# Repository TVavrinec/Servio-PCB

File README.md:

# Servio PCB

| pin | function | description |
| --- | -------- | ---- |
| C1  | GND | ground for main connector |
| C2  | VCC | input power for main connector |
| C3  | TX | UART communication TX pin |
| C4  | RX | UART communication RX pin |
| S1  | ENC.CLK,POT.OUT | CLK for SPI encoder, input pin for potentiometer |
| S2  | ENC.MISO,QE.CHB | MISO for SPI encoder, B channel for quadrature encoder |
| S3  | ENC.MOSI,QE.CHA | MOSI for SPI encoder, A channel for quadrature encoder |
| S4  | GND | GND for side connector |
| S5  | VDD 3V3 | MCU voltage for side connector |
| M1  | M1 | motor pin 1 |
| M2  | M2 | motor pin 2 |
| B1  | VDD 3V3 | voltage for boot mode |
| B2  | BOOT0 | pin triggering boot mode |

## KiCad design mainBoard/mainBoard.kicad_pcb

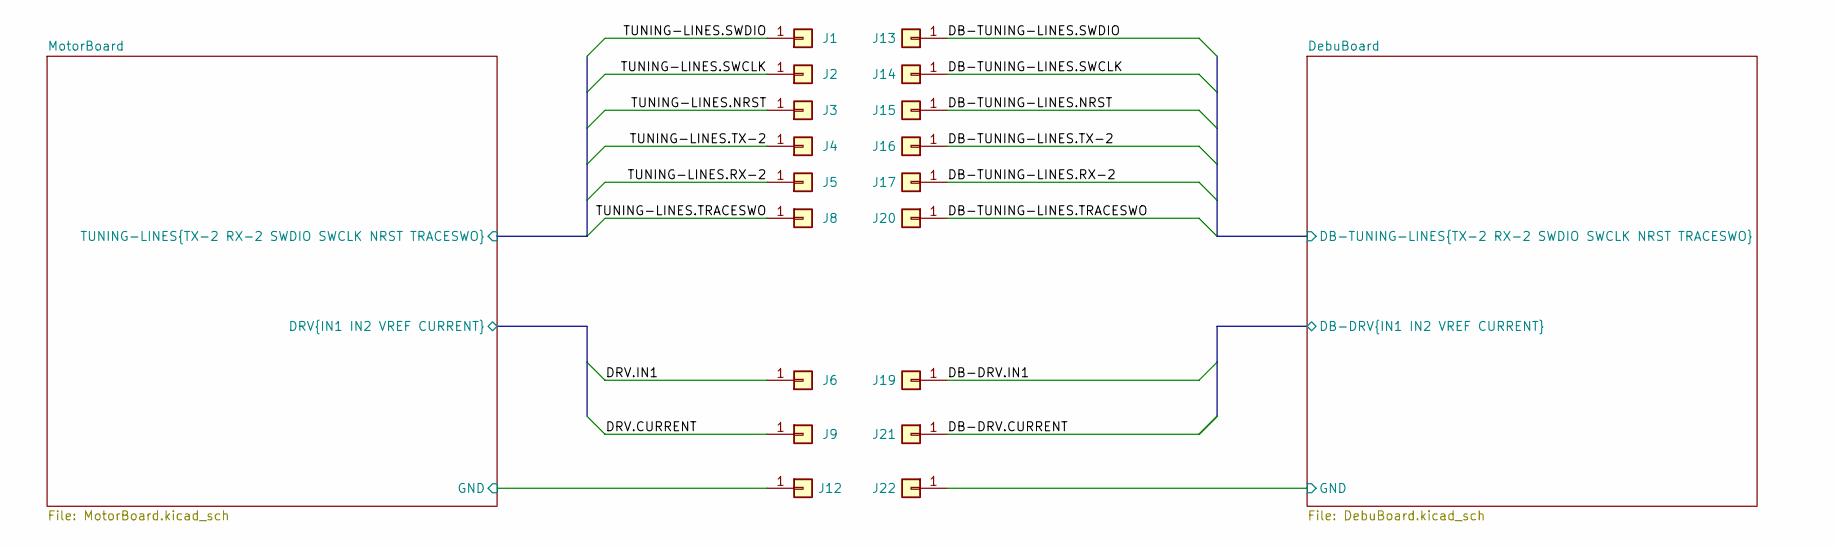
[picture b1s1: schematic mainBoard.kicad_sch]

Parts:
J1, J2, J3, J4, J5, J6, J8, J9, J12: Conn_01x01; YZ157015035P-01-contact_pad; JLCPCB_IGNORE 1
J13, J14, J15, J16, J17, J19, J20, J21, J22: Conn_01x01; YZ157015035P-01; LCSC C5157325

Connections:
/DebuBoard/DB-DRV.CURRENT: J21.1; also elsewhere on the board
/DebuBoard/DB-DRV.IN1: J19.1; also elsewhere on the board
/DebuBoard/DB-TUNING-LINES.NRST: J15.1; also elsewhere on the board
/DebuBoard/DB-TUNING-LINES.RX-2: J17.1; also elsewhere on the board
/DebuBoard/DB-TUNING-LINES.SWCLK: J14.1; also elsewhere on the board
/DebuBoard/DB-TUNING-LINES.SWDIO: J13.1; also elsewhere on the board
/DebuBoard/DB-TUNING-LINES.TRACESWO: J20.1; also elsewhere on the board
/DebuBoard/DB-TUNING-LINES.TX-2: J16.1; also elsewhere on the board
/DebuBoard/GND: J22.1; also elsewhere on the board
/MotorBoard/DRV.CURRENT: J9.1; also elsewhere on the board
/MotorBoard/DRV.IN1: J6.1; also elsewhere on the board
/MotorBoard/TUNING-LINES.NRST: J3.1; also elsewhere on the board
/MotorBoard/TUNING-LINES.RX-2: J5.1; also elsewhere on the board
/MotorBoard/TUNING-LINES.SWCLK: J2.1; also elsewhere on the board
/MotorBoard/TUNING-LINES.SWDIO: J1.1; also elsewhere on the board
/MotorBoard/TUNING-LINES.TRACESWO: J8.1; also elsewhere on the board
/MotorBoard/TUNING-LINES.TX-2: J4.1; also elsewhere on the board
GND: J12.1; also elsewhere on the board

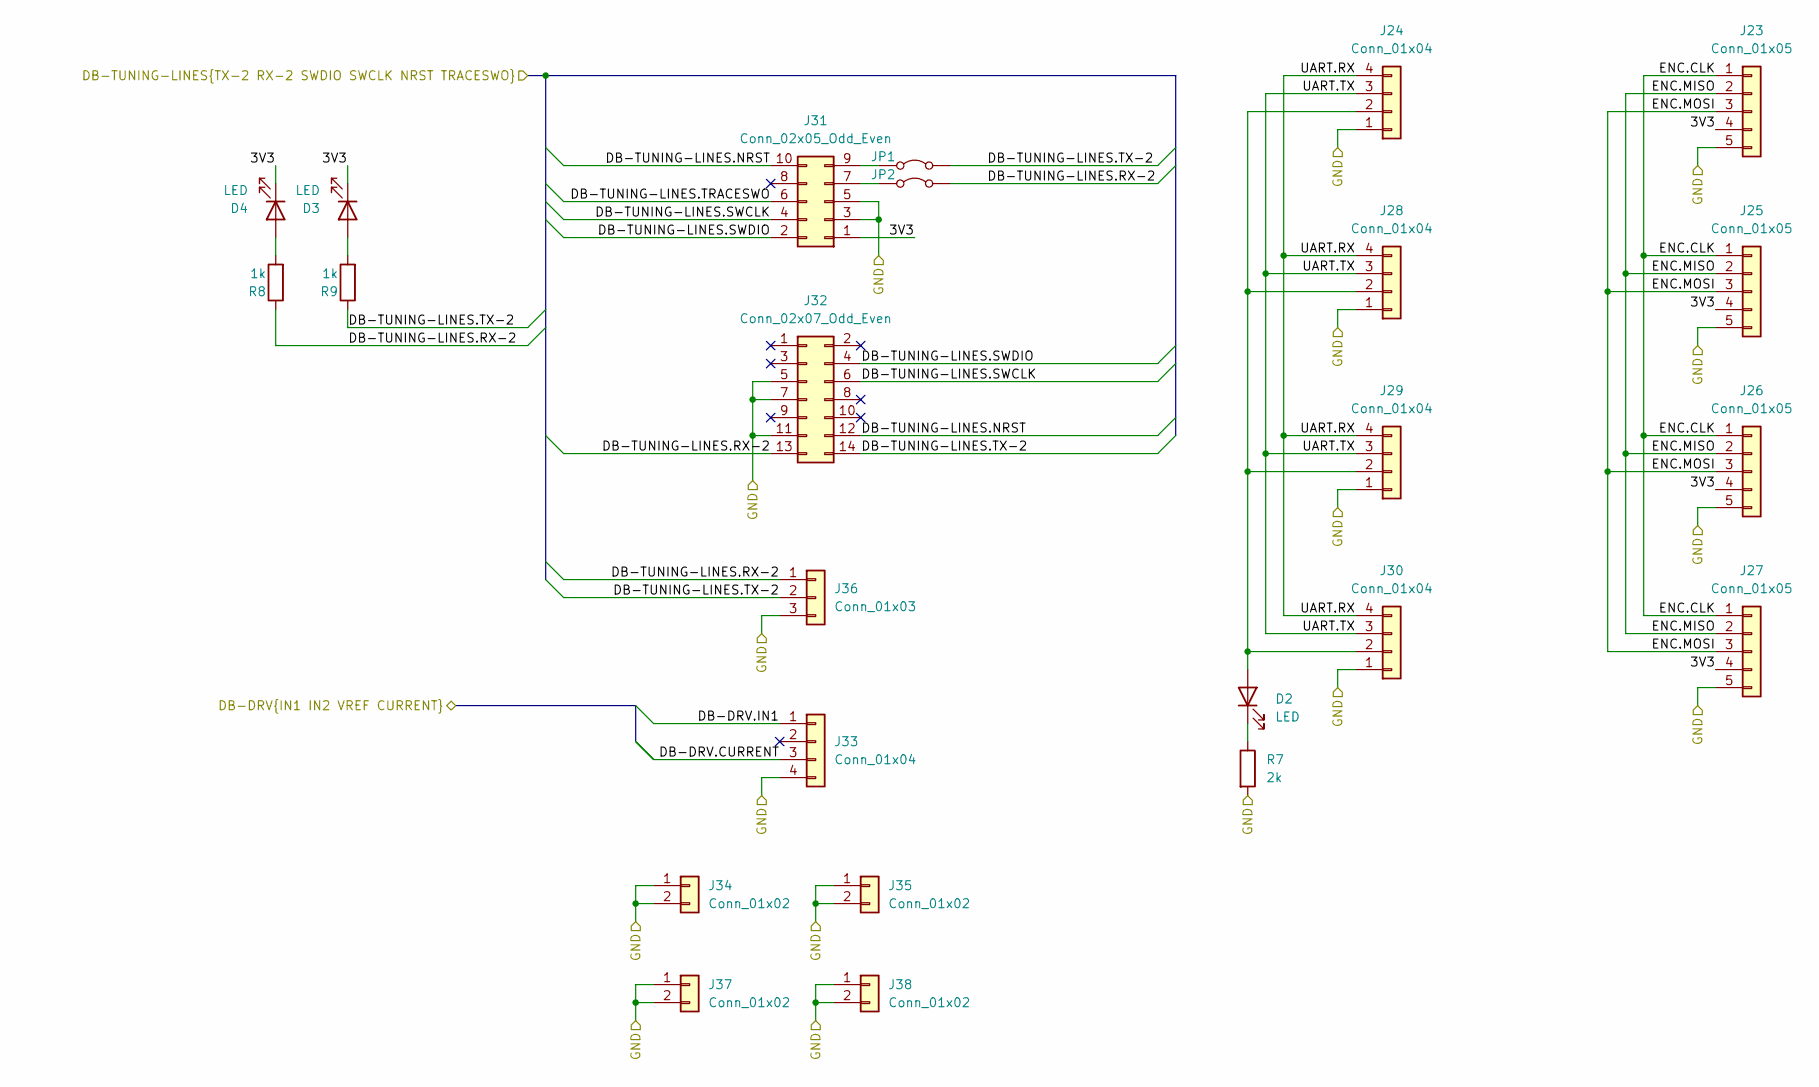
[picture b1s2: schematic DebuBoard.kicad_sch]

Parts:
D2, D3, D4: LED; LED_0603_1608Metric; LCSC C7496820
J23, J25, J26, J27: Conn_01x05; PinHeader_1x05_P2.00mm_Vertical; LCSC C7501286
J24, J28, J29, J30: Conn_01x04; JST_PH_B4B-PH-K_1x04_P2.00mm_Vertical; LCSC C20598724
J31: Conn_02x05_Odd_Even; PinHeader_2x05_P1.27mm_Vertical; LCSC C239059
J32: Conn_02x07_Odd_Even; PinHeader_2x07_P1.27mm_Vertical; LCSC C783845
J33: Conn_01x04; PinHeader_1x04_P2.54mm_Vertical; LCSC C2691448
J34, J35, J37, J38: Conn_01x02; PinHeader_1x02_P2.54mm_Vertical; LCSC C492401
J36: Conn_01x03; PinHeader_1x03_P2.54mm_Vertical; LCSC C49257
JP1, JP2: Jumper_2_Bridged; SolderJumper-2_P1.3mm_Open_TrianglePad1.0x1.5mm
R7: 2k; C_0603_1608Metric; LCSC C22975
R8, R9: 1k; C_0603_1608Metric; LCSC C21190

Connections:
/DebuBoard/3V3: D3.1 (K), D4.1 (K), J23.4, J25.4, J26.4, J27.4, J31.1
/DebuBoard/DB-DRV.CURRENT: J33.3; also elsewhere on the board
/DebuBoard/DB-DRV.IN1: J33.1; also elsewhere on the board
/DebuBoard/DB-TUNING-LINES.NRST: J31.10, J32.12; also elsewhere on the board
/DebuBoard/DB-TUNING-LINES.RX-2: J32.13, J36.1, JP2.2 (B), R8.1; also elsewhere on the board
/DebuBoard/DB-TUNING-LINES.SWCLK: J31.4, J32.6; also elsewhere on the board
/DebuBoard/DB-TUNING-LINES.SWDIO: J31.2, J32.4; also elsewhere on the board
/DebuBoard/DB-TUNING-LINES.TRACESWO: J31.6; also elsewhere on the board
/DebuBoard/DB-TUNING-LINES.TX-2: J32.14, J36.2, JP1.2 (B), R9.1; also elsewhere on the board
/DebuBoard/ENC.CLK: J23.1, J25.1, J26.1, J27.1
/DebuBoard/ENC.MISO: J23.2, J25.2, J26.2, J27.2
/DebuBoard/ENC.MOSI: J23.3, J25.3, J26.3, J27.3
/DebuBoard/GND: J23.5, J24.1, J25.5, J26.5, J27.5, J28.1, J29.1, J30.1, J31.3, J31.5, J32.5, J32.7, J32.11, J33.4, J34.1, J34.2, J35.1, J35.2, J36.3, J37.1, J37.2, J38.1, J38.2, R7.2; also elsewhere on the board
/DebuBoard/UART.RX: J24.4, J28.4, J29.4, J30.4
/DebuBoard/UART.TX: J24.3, J28.3, J29.3, J30.3
unnamed: D2.2 (A), J24.2, J28.2, J29.2, J30.2
unnamed: D2.1 (K), R7.1
unnamed: D3.2 (A), R9.2
unnamed: D4.2 (A), R8.2
unnamed: J31.7, JP2.1 (A)
unnamed: J31.9, JP1.1 (A)

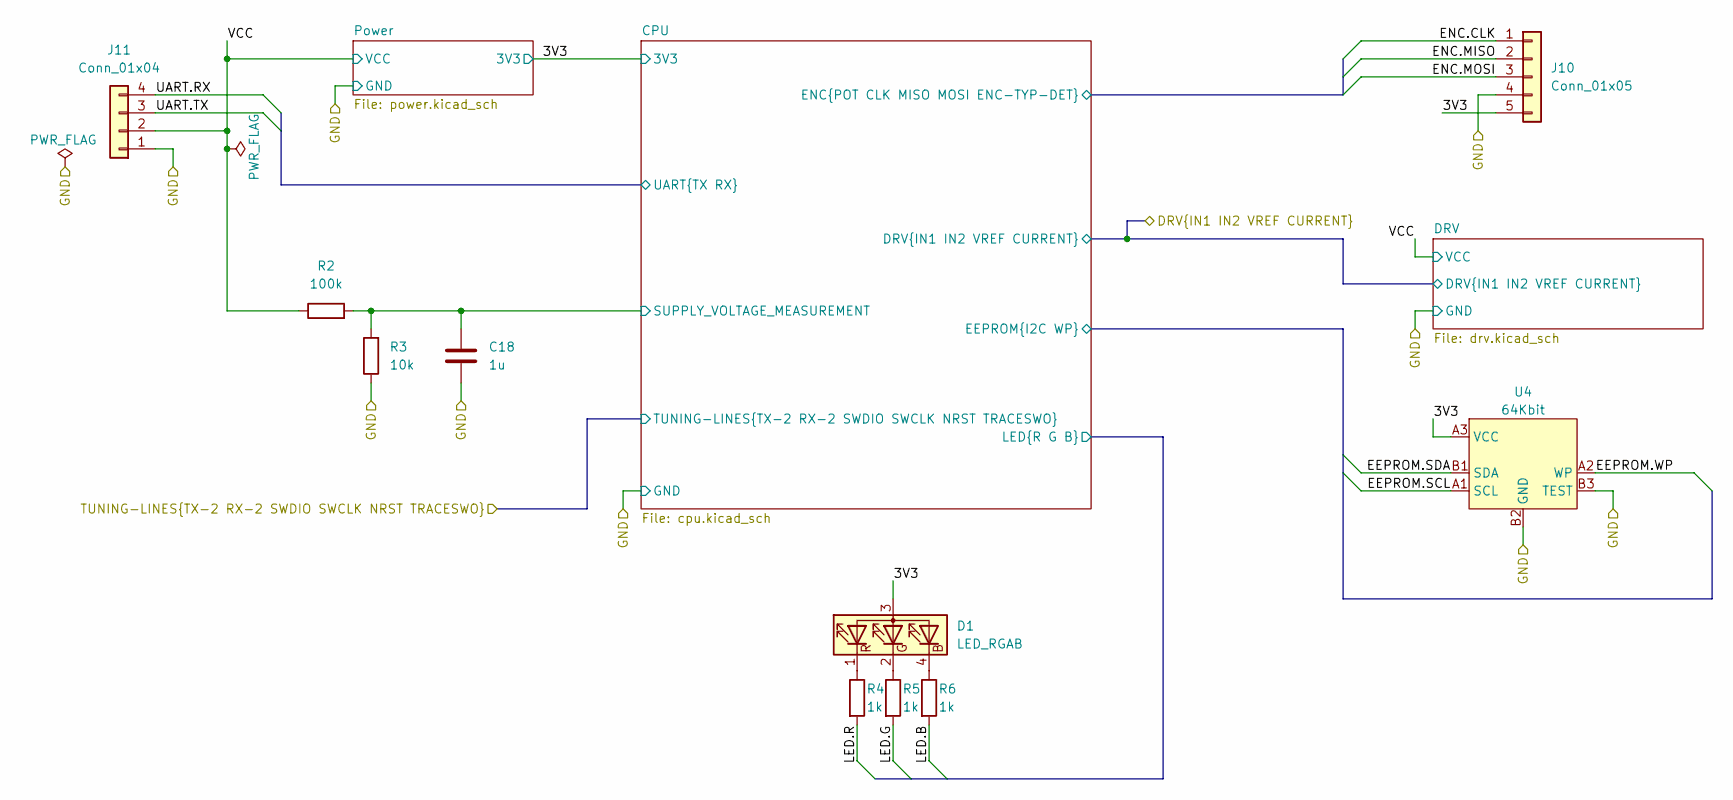
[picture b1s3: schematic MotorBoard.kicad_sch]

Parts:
C18: 1u; C_0402_1005Metric; LCSC C52923
D1: LED_RGAB; LED_LiteOn_LTST-C19HE1WT; LCSC C965840
J10: Conn_01x05; PinHeader_1x05_P2.00mm_Vertical; LCSC C7501286
J11: Conn_01x04; JST_PH_B4B-PH-K_1x04_P2.00mm_Vertical; LCSC C20598724
R2: 100k; R_0201_0603Metric; LCSC C320497
R3: 10k; R_0201_0603Metric; LCSC C473048
R4, R5, R6: 1k; C_0201_0603Metric; LCSC C138165
U4: 64Kbit; XFBGA-6; LCSC C123068

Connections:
/MotorBoard/CPU/EEPROM.SCL: U4.A1 (SCL); also elsewhere on the board
/MotorBoard/CPU/EEPROM.SDA: U4.B1 (SDA); also elsewhere on the board
/MotorBoard/CPU/EEPROM.WP: U4.A2 (WP); also elsewhere on the board
/MotorBoard/CPU/ENC.CLK: J10.1; also elsewhere on the board
/MotorBoard/CPU/ENC.MISO: J10.2; also elsewhere on the board
/MotorBoard/CPU/ENC.MOSI: J10.3; also elsewhere on the board
/MotorBoard/CPU/LED.B: R6.2; also elsewhere on the board
/MotorBoard/CPU/LED.G: R5.2; also elsewhere on the board
/MotorBoard/CPU/LED.R: R4.2; also elsewhere on the board
/MotorBoard/CPU/SUPPLY_VOLTAGE_MEASUREMENT: C18.1, R2.2, R3.2; also elsewhere on the board
/MotorBoard/CPU/UART.RX: J11.4; also elsewhere on the board
/MotorBoard/CPU/UART.TX: J11.3; also elsewhere on the board
/MotorBoard/VCC: J11.2, R2.1; also elsewhere on the board
GND: C18.2, J10.4, J11.1, R3.1, U4.B2 (GND), U4.B3 (TEST); also elsewhere on the board
unnamed: D1.4 (BK), R6.1
unnamed: D1.2 (GK), R5.1
unnamed: D1.1 (RK), R4.1
VDD: D1.3 (A), J10.5, U4.A3 (VCC); also elsewhere on the board

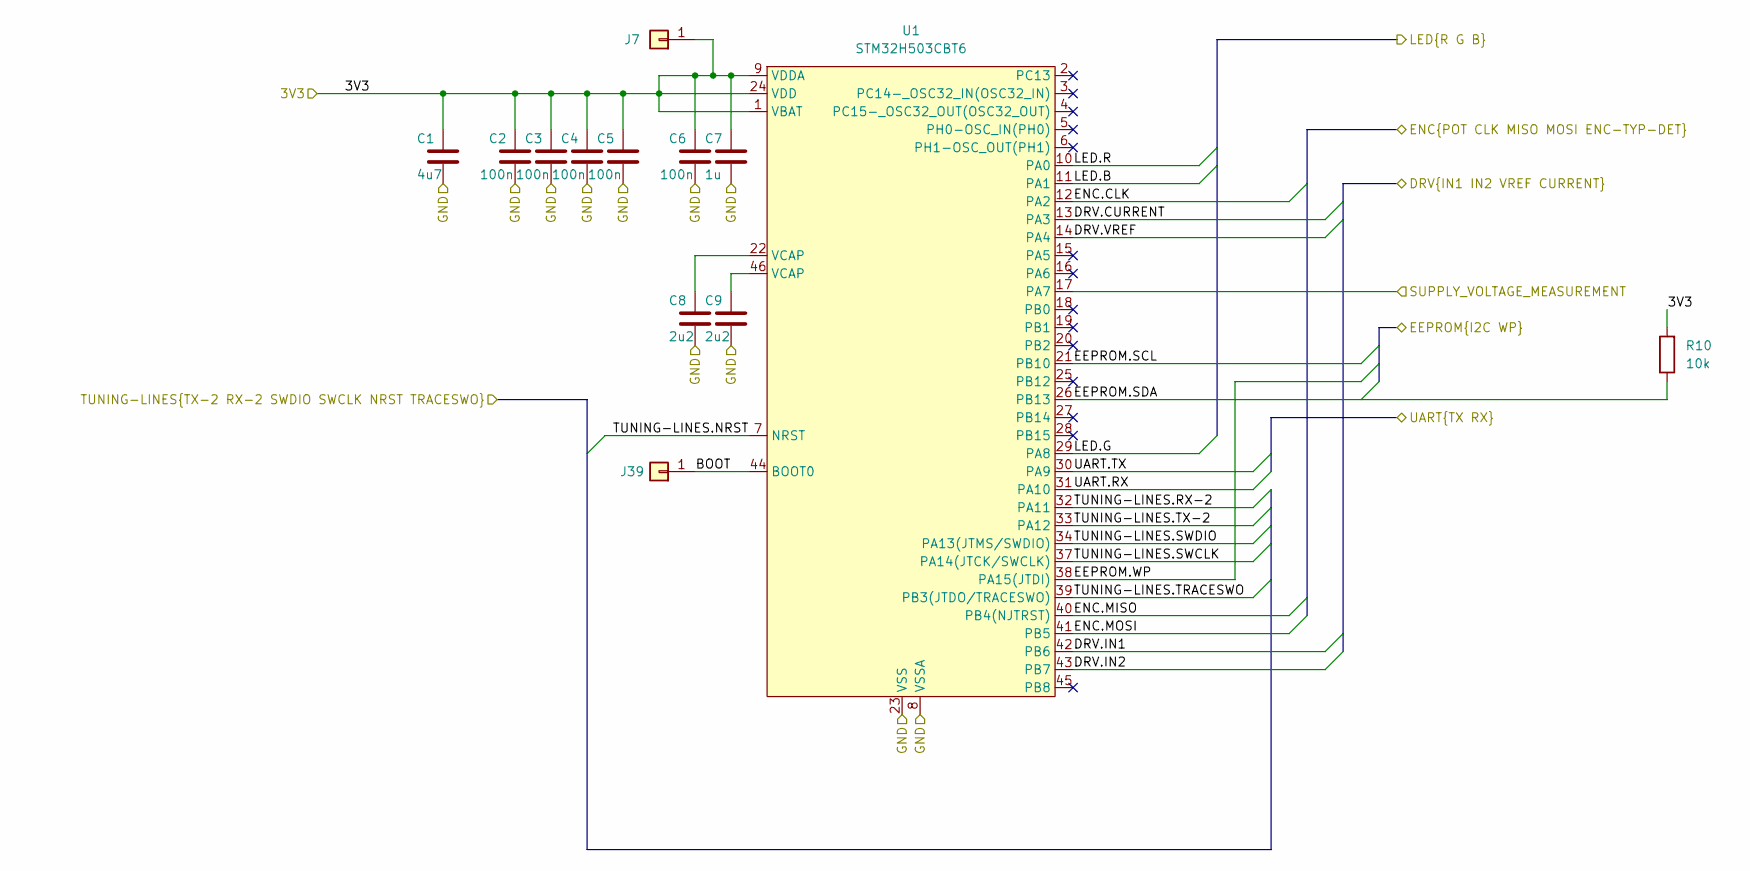
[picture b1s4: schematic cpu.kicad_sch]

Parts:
C1: 4u7; C_0402_1005Metric; LCSC C23733
C2, C3, C4, C5, C6: 100n; C_0201_0603Metric; LCSC C76934
C7: 1u; C_0402_1005Metric; LCSC C52923
C8, C9: 2u2; C_0402_1005Metric; LCSC C342966
J7, J39: Conn_01x01; YZ157015035P-01-contact_pad; JLCPCB_IGNORE 1
R10: 10k; R_0201_0603Metric; LCSC C473048
U1: STM32H503CBT6; LQFP-48_7x7mm_P0.5mm; LCSC C17700273

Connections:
/MotorBoard/CPU/BOOT: J39.1, U1.44 (BOOT0)
/MotorBoard/CPU/EEPROM.SCL: U1.21 (PB10); also elsewhere on the board
/MotorBoard/CPU/EEPROM.SDA: R10.1, U1.26 (PB13); also elsewhere on the board
/MotorBoard/CPU/EEPROM.WP: U1.38 (PA15(JTDI)); also elsewhere on the board
/MotorBoard/CPU/ENC.CLK: U1.12 (PA2); also elsewhere on the board
/MotorBoard/CPU/ENC.MISO: U1.40 (PB4(NJTRST)); also elsewhere on the board
/MotorBoard/CPU/ENC.MOSI: U1.41 (PB5); also elsewhere on the board
/MotorBoard/CPU/LED.B: U1.11 (PA1); also elsewhere on the board
/MotorBoard/CPU/LED.G: U1.29 (PA8); also elsewhere on the board
/MotorBoard/CPU/LED.R: U1.10 (PA0); also elsewhere on the board
/MotorBoard/CPU/SUPPLY_VOLTAGE_MEASUREMENT: U1.17 (PA7); also elsewhere on the board
/MotorBoard/CPU/UART.RX: U1.31 (PA10); also elsewhere on the board
/MotorBoard/CPU/UART.TX: U1.30 (PA9); also elsewhere on the board
/MotorBoard/DRV.CURRENT: U1.13 (PA3); also elsewhere on the board
/MotorBoard/DRV.IN1: U1.42 (PB6); also elsewhere on the board
/MotorBoard/DRV.IN2: U1.43 (PB7); also elsewhere on the board
/MotorBoard/DRV.VREF: U1.14 (PA4); also elsewhere on the board
/MotorBoard/TUNING-LINES.NRST: U1.7 (NRST); also elsewhere on the board
/MotorBoard/TUNING-LINES.RX-2: U1.32 (PA11); also elsewhere on the board
/MotorBoard/TUNING-LINES.SWCLK: U1.37 (PA14(JTCK/SWCLK)); also elsewhere on the board
/MotorBoard/TUNING-LINES.SWDIO: U1.34 (PA13(JTMS/SWDIO)); also elsewhere on the board
/MotorBoard/TUNING-LINES.TRACESWO: U1.39 (PB3(JTDO/TRACESWO)); also elsewhere on the board
/MotorBoard/TUNING-LINES.TX-2: U1.33 (PA12); also elsewhere on the board
GND: C1.2, C2.2, C3.2, C4.2, C5.2, C6.2, C7.2, C8.2, C9.2, U1.8 (VSSA), U1.23 (VSS), U1.35 (VSS), U1.47 (VSS); also elsewhere on the board
unnamed: C8.1, U1.22 (VCAP)
unnamed: C9.1, U1.46 (VCAP)
VDD: C1.1, C2.1, C3.1, C4.1, C5.1, C6.1, C7.1, J7.1, R10.2, U1.1 (VBAT), U1.9 (VDDA), U1.24 (VDD), U1.36 (VDD), U1.48 (VDD); also elsewhere on the board

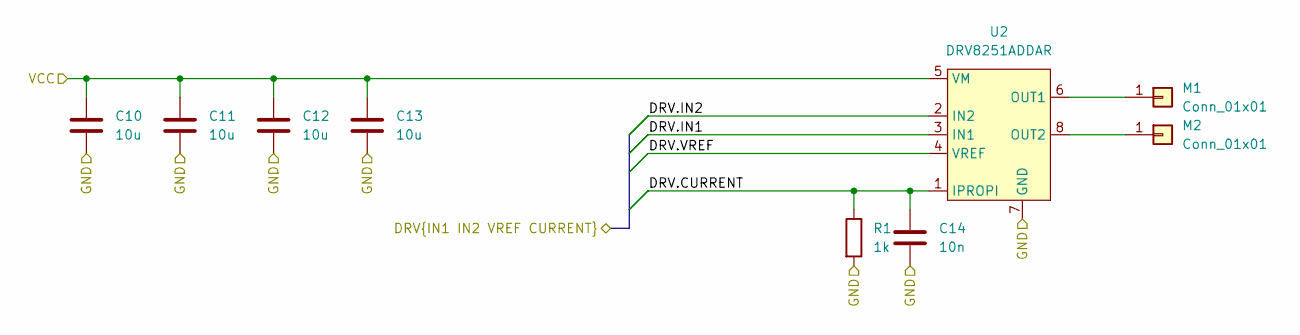
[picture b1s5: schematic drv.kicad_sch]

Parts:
C10, C11, C12, C13: 10u; C_0603_1608Metric; LCSC C194427
C14: 10n; C_0201_0603Metric; LCSC C285010
M1, M2: Conn_01x01; YZ157015035P-01-contact_pad; JLCPCB_IGNORE 1
R1: 1k; C_0201_0603Metric; LCSC C138165
U2: DRV8251ADDAR; SOIC-8-1EP_3.9x4.9mm_P1.27mm_EP2.62x3.51mm_ThermalVias; LCSC C5218844

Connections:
/MotorBoard/DRV.CURRENT: C14.1, R1.1, U2.1 (IPROPI); also elsewhere on the board
/MotorBoard/DRV.IN1: U2.3 (IN1); also elsewhere on the board
/MotorBoard/DRV.IN2: U2.2 (IN2); also elsewhere on the board
/MotorBoard/DRV.VREF: U2.4 (VREF); also elsewhere on the board
/MotorBoard/VCC: C10.1, C11.1, C12.1, C13.1, U2.5 (VM); also elsewhere on the board
GND: C10.2, C11.2, C12.2, C13.2, C14.2, R1.2, U2.7 (GND), U2.9 (GND); also elsewhere on the board
unnamed: M1.1, U2.6 (OUT1)
unnamed: M2.1, U2.8 (OUT2)

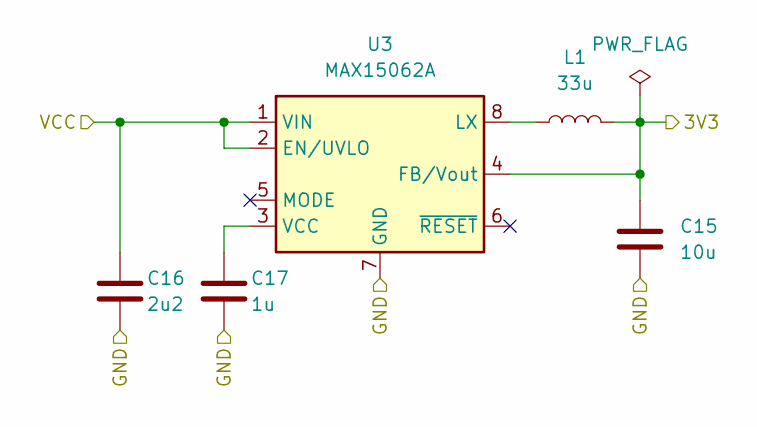
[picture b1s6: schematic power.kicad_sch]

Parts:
C15: 10u; C_0603_1608Metric; LCSC C194427
C16: 2u2; C_0402_1005Metric; LCSC C342966
C17: 1u; C_0402_1005Metric; LCSC C52923
L1: 33u; L_1008_2520Metric; LCSC C223363
U3: MAX15062A; DFN-8_2x2mm_P0.5mm; LCSC C2846801

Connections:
/MotorBoard/VCC: C16.1, U3.1 (VIN), U3.2 (EN/UVLO); also elsewhere on the board
GND: C15.2, C16.2, C17.2, U3.7 (GND); also elsewhere on the board
unnamed: L1.1, U3.8 (LX)
unnamed: C17.1, U3.3 (VCC)
VDD: C15.1, L1.2, U3.4 (FB/Vout); also elsewhere on the board

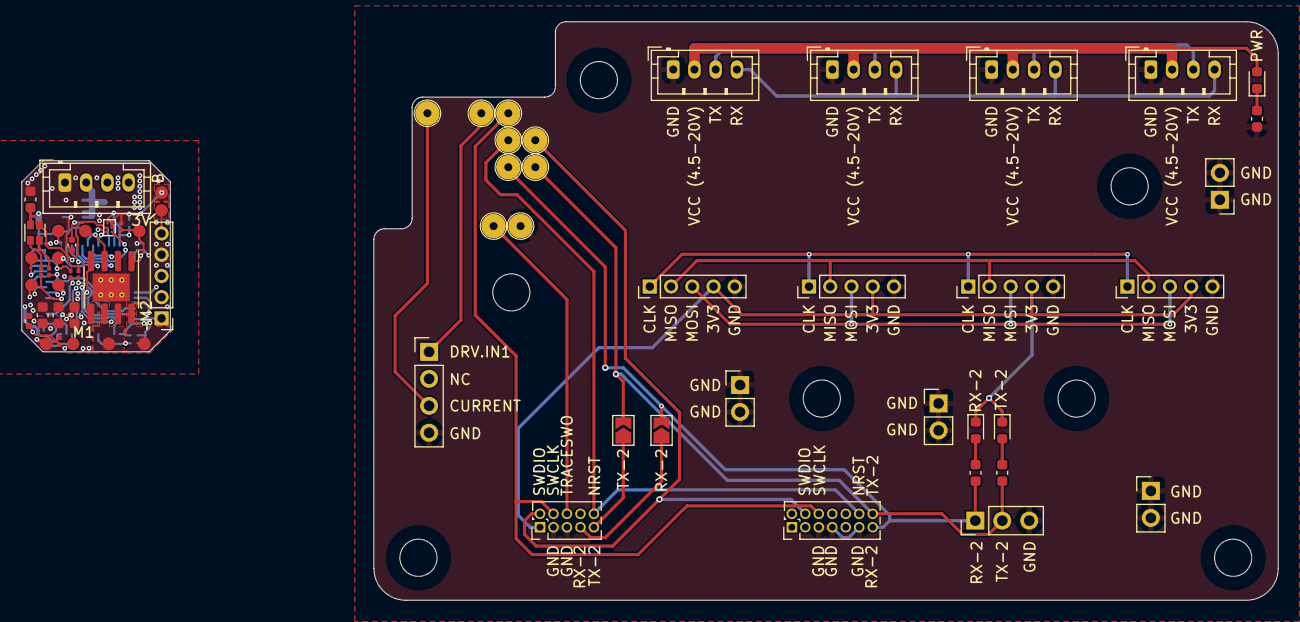
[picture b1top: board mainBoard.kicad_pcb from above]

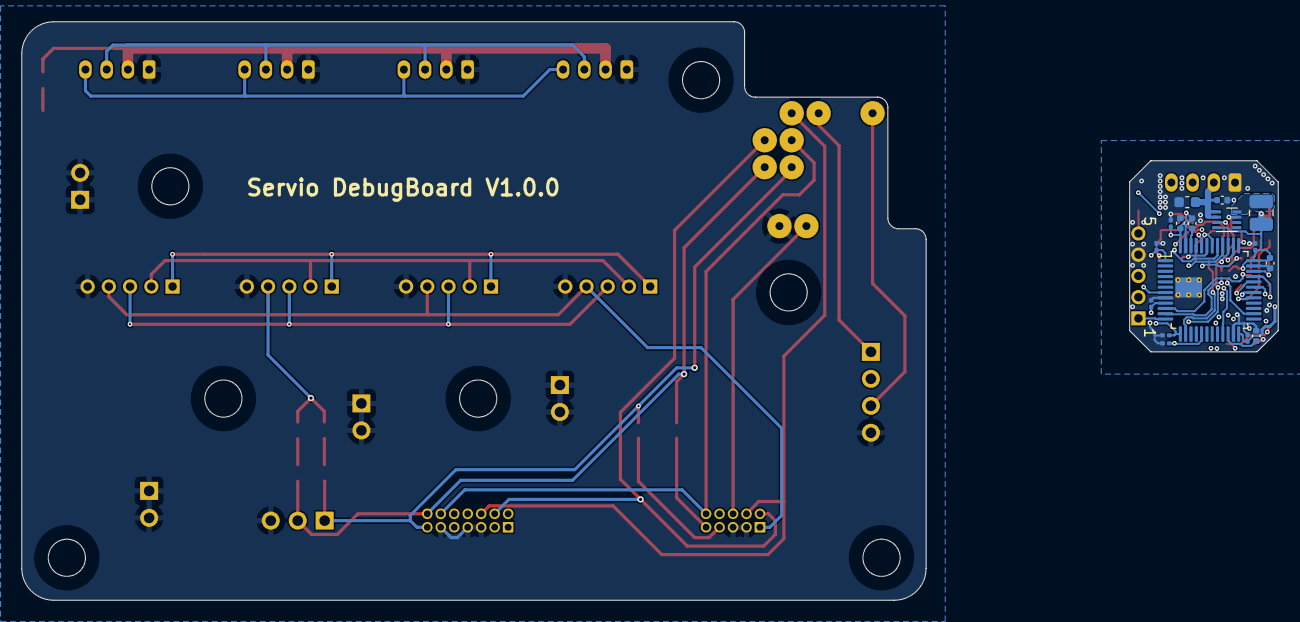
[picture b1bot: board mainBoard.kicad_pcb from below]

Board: 4 copper layers, 118.4 x 54.5 mm, 79 parts (16 on the bottom side), 56 nets.

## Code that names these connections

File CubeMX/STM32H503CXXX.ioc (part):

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Mcu.Name=STM32H503CBTx
Mcu.Package=LQFP48
Mcu.UserName=STM32H503CBTx
PA0.GPIOParameters=GPIO_Label
PA0.GPIO_Label=POT_ADC
PA0.Signal=ADCx_INP0
PA1.Signal=S_TIM2_CH2
PA10.Mode=Asynchronous
PA10.Signal=USART1_RX
PA11.Mode=Asynchronous
PA11.Signal=USART2_RX
PA12.Mode=Asynchronous
PA12.Signal=USART2_TX
PA13(JTMS/SWDIO).Signal=DEBUG_JTMS-SWDIO
PA14(JTCK/SWCLK).Signal=DEBUG_JTCK-SWCLK
PA15(JTDI).GPIOParameters=GPIO_Label
PA15(JTDI).GPIO_Label=EEPROM-WP
PA15(JTDI).Signal=GPIO_Output
PA2.Signal=S_TIM3_ETR
PA3.GPIOParameters=GPIO_Label
PA3.GPIO_Label=CURR_ADC
PA3.Signal=ADCx_INP15
PA4.Signal=COMP_DAC11_group
PA7.Signal=ADCx_INP7
PA9.Mode=Asynchronous
PA9.Signal=USART1_TX
PB10.Signal=S_TIM2_CH3
PB2.Signal=S_TIM2_CH1
PB3(JTDO/TRACESWO).Signal=I2C2_SCL
PB4(NJTRST).Signal=S_TIM3_CH1
PB5.Signal=S_TIM3_CH2
PB6.GPIOParameters=GPIO_Label
PB6.GPIO_Label=HBRIDGE_A
PB6.Signal=S_TIM1_CH2
PB7.GPIOParameters=GPIO_Label
PB7.GPIO_Label=HBRIDGE_B
PB7.Signal=S_TIM1_CH1
PB8.Signal=I2C2_SDA
RCC.HSE_VALUE=25000000
RCC.SYSCLKFreq_VALUE=32000000
board=custom

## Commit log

2023-09-16 Specifikace
2023-09-16 CubeMX
2023-09-16 v1 feedback
2023-09-16 V1 feedback
    PWM na LED a měření naoájecího napětí
2023-09-23 Část schématu
2023-12-05 LEDky, měření napájení, připojení DRV atd.
2023-12-05 Pouzdra
2023-12-05 test-pointy a zdvojení konektorů
2023-12-05 test-point na děliči
2023-12-05 test-pointy na ENC-POT
2023-12-24 Lepší GND
2023-12-24 happy christmas
2023-12-24 Popisky
2023-12-25 Zvetšení test pointů
2023-12-25 Hrádky s poligony
2023-12-28 JST-XH na externí motorový konektor
2023-12-28 Moc kondíků
2023-12-28 GNDDETECT
2023-12-29 16x20
2023-12-29 Otočitelnost
2024-01-21 Větší via
2024-05-30 updated the spec
2024-06-11 CubeMX V2
2024-06-13 drobeček
2024-07-01 ukild
2024-07-25 DebugBoard
2024-07-27 Add power LEDs and UART connector
2024-07-27 Reducing size of debug board
2024-07-27 Fix GND polygon
2024-07-27 Mounting holes and recessing the main board
2024-07-27 Corners
2024-08-07 Add LCSC code
2024-08-07 Add GND via for better cooling
2024-09-05 LCSC cods
2024-11-16 Bigger via
2024-11-16 updatez
2024-11-24 New C1 LCSC cod
2025-03-19 Kicad 8 and SDA pullup
2025-03-20 SDA pullup add to PCB
2025-03-20 Change pin configuration for encoder header
2025-03-20 Expose boot0 so any user can shortcut to VCC
2025-03-20 On debug board, For BMDU connector (J31) - make TX/RX wiring optional
2025-03-20 On debug board: vire VRef (3v3) to the BMDU connector
2025-03-20 Increasing motor pedals
2025-03-23 Makefile
2025-09-05 after-release fixes
2025-09-05 Remove the GND tuning pad and replace them with VDD tuning pads, and update to Kicad 9.0
2025-09-05 Pad labels
2025-09-05 LCSC cod of inductor
2026-01-24 dropped spec. added readme and diag
2026-01-24 added more dims
2026-01-24 fixed background
2026-01-24 basic pin description
2026-01-24 dropped spec. added readme and diag (#25)
    * dropped spec. added readme and diag
    * added more dims
    * fixed background
    * basic pin description
